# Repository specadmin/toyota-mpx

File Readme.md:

### Description ###

This library is a software driver for MPX (BEAN) bus interface, designed by Toyota and used in some Toyota and Lexus cars. Find the content of the [docs](https://github.com/specadmin/toyota-mpx/tree/master/docs) folder for better understanding of this bus.
The driver works in asynchonous mode and does not block other routings, while MPX packets are being received or transmited.

You may found some MPX packets' description [here](MPX-codes.md).

### Features ###

* Asynchronous receiver
* Asynchronous transmitter
* Independent receiption and transmission
* Arbitration control
* Transmission FIFO queue
* Configurable pins
* Easy timer select

### Physical layer ###

<div align="center">  </div>

### Requirements ###

 * AVR MPU;
 * 12 MHz or higher clock frequency;
 * one external interrupt (PCINT may be used, but not tested yet);
 * one 8 bit timer;
 * GNU AVR C compiller (avr-gcc);

### Limitations ###

 * The driver has NO it's own address. So it receives all the packets, that are being transmited in the MPX network. The driver does NOT filter any packets and does NOT send acknowlegement to any packets.

### Documentation ###

There is no any special documentation for this library. The library code was written to be efficient and clear for your understanding, so it is full of comments. See the [header file](https://github.com/specadmin/toyota-mpx/blob/master/mpx.h) for methods descriptions. Also you may find a [sample project](https://github.com/specadmin/toyota-mpx/tree/master/samples/MPX-dev-board), that uses this library, inside.

### Usage example ###

```
void mpxReceiver(BYTE size, const BYTE* buf)
{
    // make something with received packet

    ...
}

int main()
{
    ...

    mpx_init(mpxReceiver);
    enable_interrupts();

    BYTE data[] = { 0xCD, 0x48 };
    mpx_send(6, 0xFE, sizeof(data), data);

    ...
}
```

### Adding to your project ###

The library is managed as a git submodule. Please refer to git submodule documentation for better understanding.

 * Run the following command in your project's root directory to clone the library:

`git submodule add https://github.com/specadmin/toyota-mpx lib/toyota-mpx`

 * Include the library's header file, where you need it:

`#include "lib/toyota-mpx/mpx.h"`

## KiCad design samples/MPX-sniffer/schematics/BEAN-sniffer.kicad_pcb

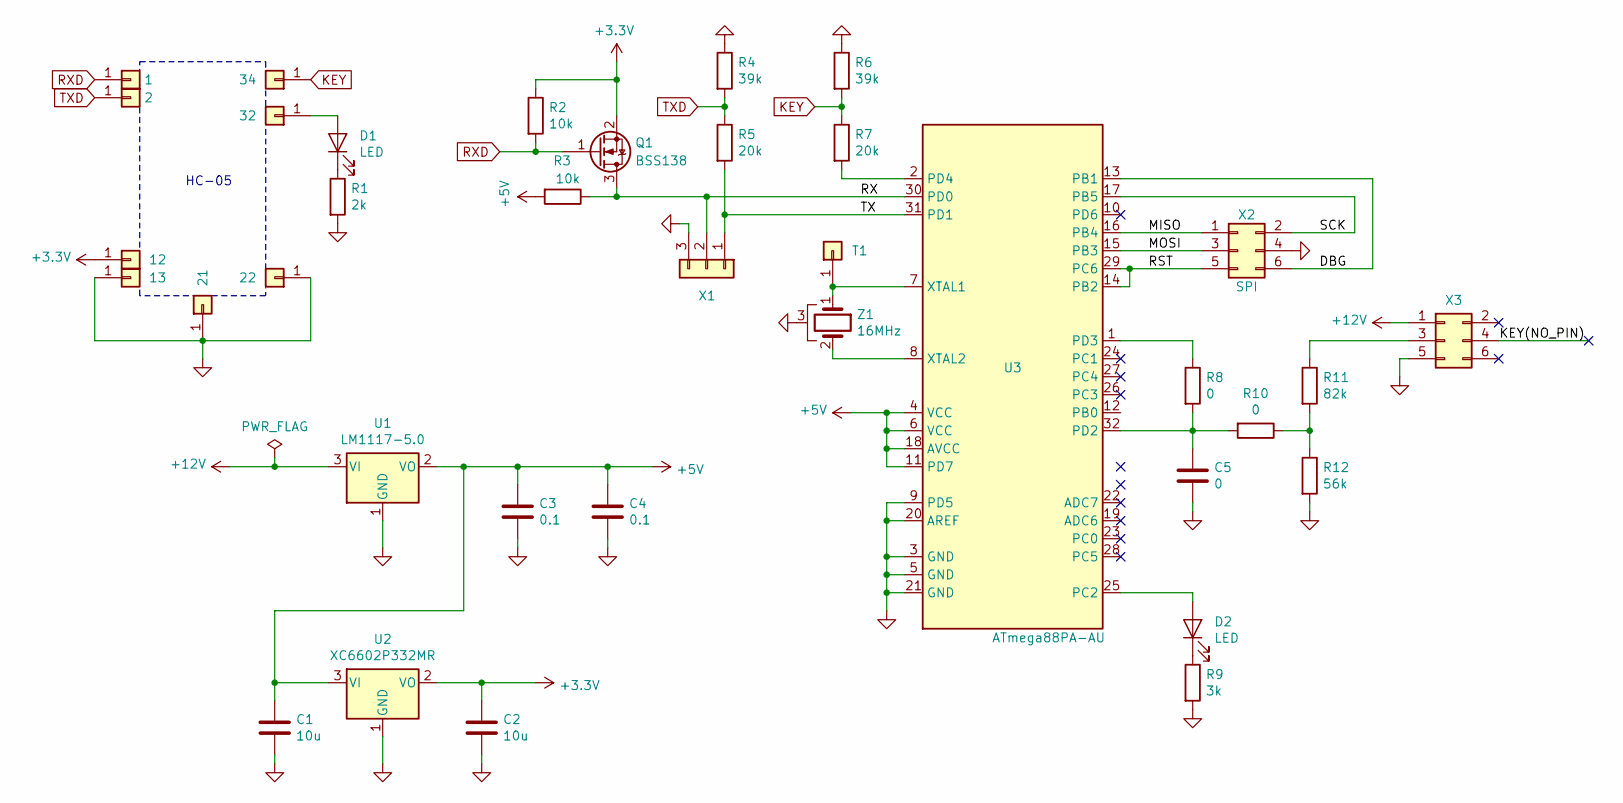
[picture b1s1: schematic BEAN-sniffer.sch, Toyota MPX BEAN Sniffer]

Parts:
C1, C2: 10u; C_0603_1608Metric_Pad1.05x0.95mm_HandSolder
C3, C4: 0.1; C_0603_1608Metric_Pad1.05x0.95mm_HandSolder
C5: 0; C_0603_1608Metric_Pad1.05x0.95mm_HandSolder
D1, D2: LED; LED_0603_1608Metric_Pad1.05x0.95mm_HandSolder
P1, P2, P3, P4, P5, P6, P7, P8: Conn_01x01; TestPoint_THTPad_D1.0mm_Drill0.5mm
Q1: BSS138; SOT-23
R1: 2k; R_0603_1608Metric_Pad1.05x0.95mm_HandSolder
R2, R3: 10k; R_0603_1608Metric_Pad1.05x0.95mm_HandSolder
R4, R6: 39k; R_0603_1608Metric_Pad1.05x0.95mm_HandSolder
R5, R7: 20k; R_0603_1608Metric_Pad1.05x0.95mm_HandSolder
R8, R10: 0; R_0603_1608Metric_Pad1.05x0.95mm_HandSolder
R9: 3k; R_0603_1608Metric_Pad1.05x0.95mm_HandSolder
R11: 82k; R_0603_1608Metric_Pad1.05x0.95mm_HandSolder
R12: 56k; R_0603_1608Metric_Pad1.05x0.95mm_HandSolder
T1: Conn_01x01; TestPoint_Pad_D1.0mm
U1: LM1117-5.0; SOT-223-3_TabPin2
U2: XC6602P332MR; SOT-23
U3: ATmega88PA-AU; TQFP-32_7x7mm_P0.8mm
X1: Conn_01x03; PinHeader_1x03_P2.54mm_Vertical
X2: SPI; PinHeader_2x03_P2.54mm_Vertical
X3: Conn_02x03_Odd_Even; PinHeader_2x03_P2.54mm_Horizontal
Z1: 16MHz; Murata_CSTCExxxxV_3213_crystal

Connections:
+3V3: C2.1, P3.1, Q1.2 (S), R2.1, U2.2 (VO)
+5V: C1.1, C3.1, C4.1, R3.2, U1.2 (VO), U2.3 (VI), U3.4 (VCC), U3.6 (VCC), U3.11 (PD7), U3.18 (AVCC)
+12V: U1.3 (VI), X3.1
/DBG: U3.13 (PB1), X2.6
/KEY(NO_PIN): X3.4
/MISO: U3.16 (PB4), X2.1
/MOSI: U3.15 (PB3), X2.3
/RST: U3.14 (PB2), U3.29 (PC6), X2.5
/RX: Q1.3 (D), R3.1, U3.30 (PD0), X1.2
/SCK: U3.17 (PB5), X2.2
/TX: R5.2, U3.31 (PD1), X1.1
GND: C1.2, C2.2, C3.2, C4.2, C5.2, P4.1, P5.1, P8.1, R1.2, R4.1, R6.1, R9.2, R12.2, U1.1 (GND), U2.1 (GND), U3.3 (GND), U3.5 (GND), U3.9 (PD5), U3.20 (AREF), U3.21 (GND), X1.3, X2.4, X3.5, Z1.3
KEY: P6.1, R6.2, R7.1
unnamed: C5.1, R8.2, R10.2, U3.32 (PD2)
unnamed: D1.1 (K), R1.1
unnamed: D1.2 (A), P7.1
unnamed: D2.1 (K), R9.1
unnamed: D2.2 (A), U3.25 (PC2)
unnamed: R7.2, U3.2 (PD4)
unnamed: R8.1, U3.1 (PD3)
unnamed: R10.1, R11.2, R12.1
unnamed: R11.1, X3.3
unnamed: T1.1, U3.7 (XTAL1), Z1.1
unnamed: U3.8 (XTAL2), Z1.2
RXD: P1.1, Q1.1 (G), R2.2
TXD: P2.1, R4.2, R5.1

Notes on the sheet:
HC-05

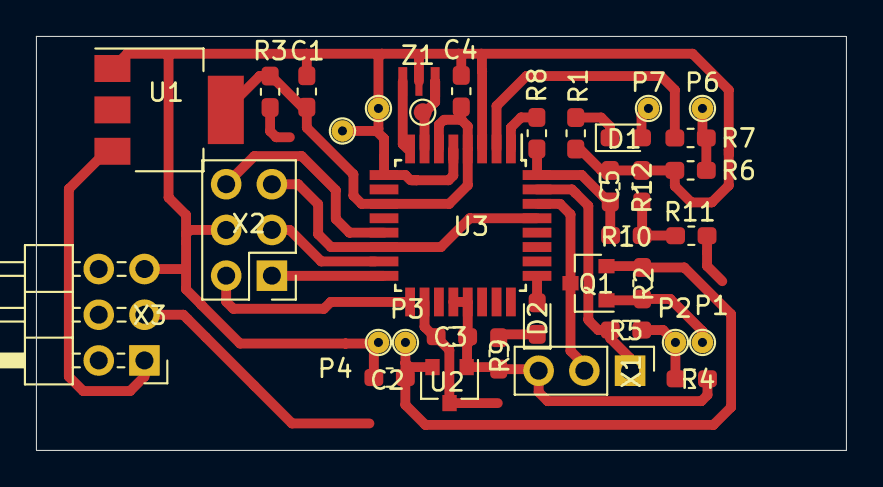
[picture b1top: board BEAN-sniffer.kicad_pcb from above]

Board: 2 copper layers, 45.0 x 23.0 mm, 36 parts (0 on the bottom side), 25 nets.

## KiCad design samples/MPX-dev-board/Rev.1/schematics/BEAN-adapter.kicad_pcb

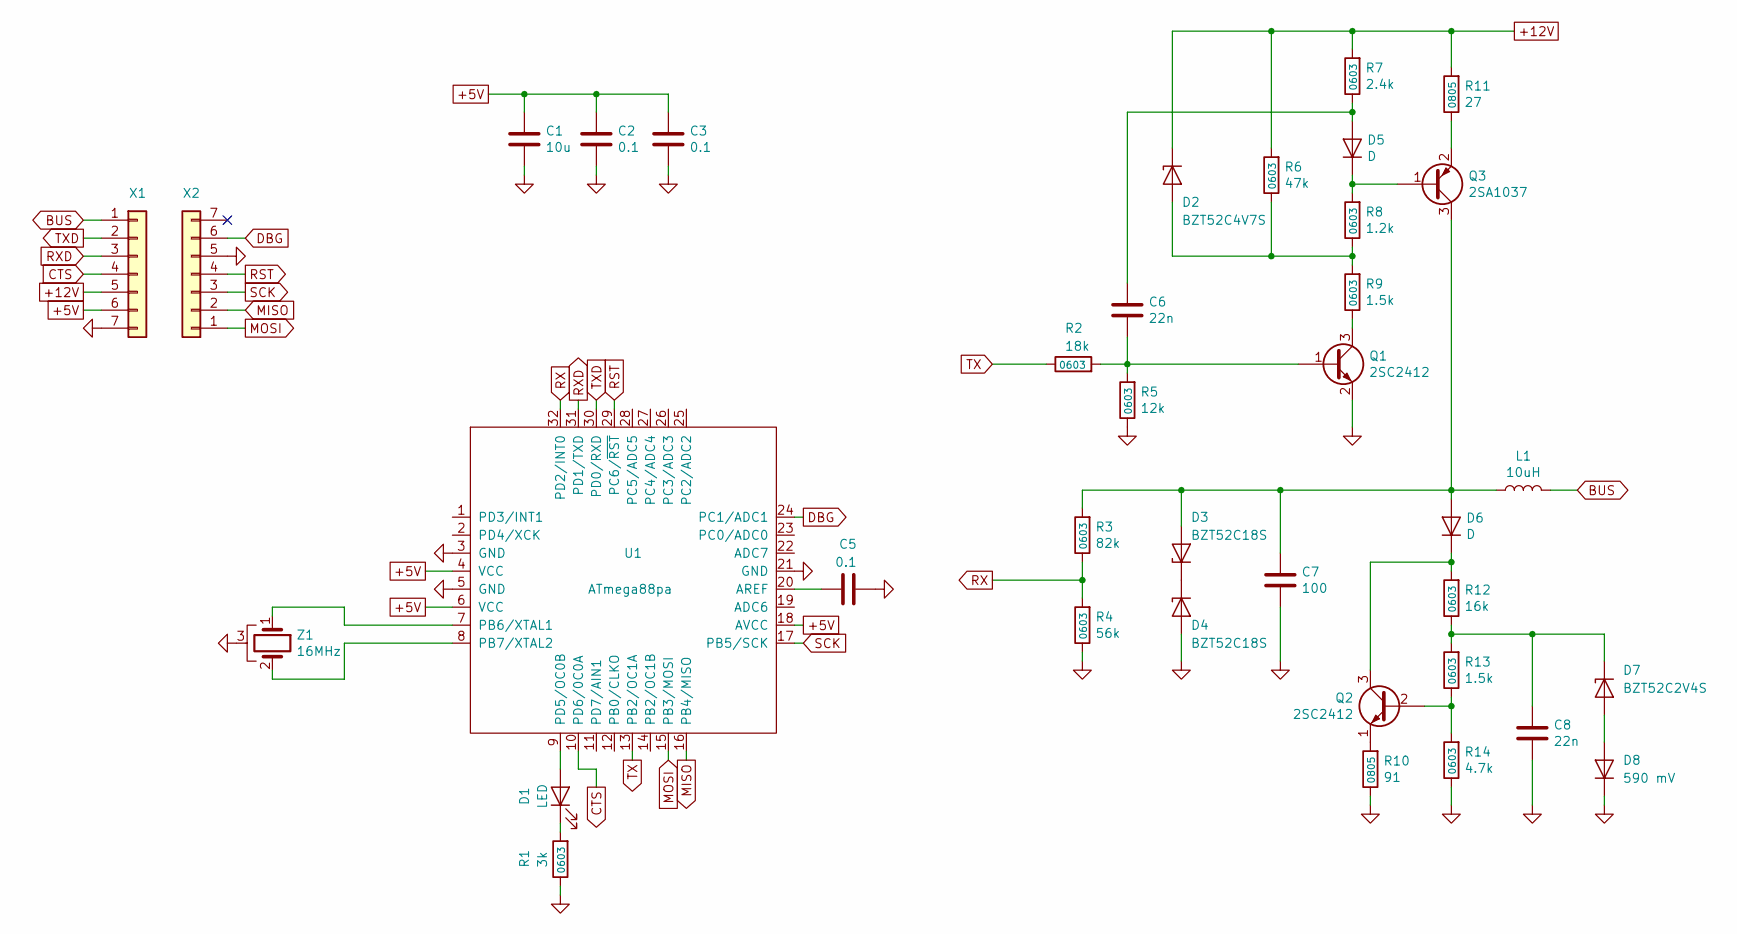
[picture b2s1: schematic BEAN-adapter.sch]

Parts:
C1: 10u; C_0603_1608Metric
C2, C3, C5: 0.1; C_0603_1608Metric
C6, C8: 22n; C_0603_1608Metric
C7: 100; C_0603_1608Metric
D1: LED; LED_0603_1608Metric
D2: BZT52C4V7S; D_SOD-323
D3, D4: BZT52C18S; D_SOD-323
D5: D; D_SOD-323
D6: D; D_SOD-110
D7: BZT52C2V4S; D_SOD-323
D8: 590 mV; D_SOD-323
L1: 10uH; L_Taiyo-Yuden_MD-3030
Q1, Q2: 2SC2412; SOT-23
Q3: 2SA1037; SOT-23
R1: 3k; R_0603_1608Metric
R2: 18k; R_0603_1608Metric
R3: 82k; R_0603_1608Metric
R4: 56k; R_0603_1608Metric
R5: 12k; R_0603_1608Metric
R6: 47k; R_0603_1608Metric
R7: 2.4k; R_0603_1608Metric
R8: 1.2k; R_0603_1608Metric
R9, R13: 1.5k; R_0603_1608Metric
R10: 91; R_0805_2012Metric
R11: 27; R_0805_2012Metric
R12: 16k; R_0603_1608Metric
R14: 4.7k; R_0603_1608Metric
U1: ATmega88pa; TQFP-32_7x7mm_P0.8mm
X1, X2: Conn_01x07; PinHeader_1x07_P2.54mm_Vertical
Z1: 16MHz; Murata_CSTCExxxxV_3213_crystal

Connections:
+5V: C1.1, C2.1, C3.1, U1.4 (VCC), U1.6 (VCC), U1.18 (AVCC), X1.6
+12V: D2.1 (K), R6.2, R7.2, R11.2, X1.5
BUS: L1.2, X1.1
CTS: U1.10 (PD6/0C0A), X1.4
DBG: U1.24 (PC1/ADC1), X2.6
GND: C1.2, C2.2, C3.2, C5.2, C7.2, C8.2, D4.2 (A), D8.1 (K), Q1.2 (E), R1.1, R4.1, R5.1, R10.1, R14.1, U1.3 (GND), U1.5 (GND), U1.21 (GND), X1.7, X2.5, Z1.3
MISO: U1.16 (PB4/MISO), X2.2
MOSI: U1.15 (PB3/MOSI), X2.1
unnamed: C5.1, U1.20 (AREF)
unnamed: C6.1, D5.2 (A), R7.1
unnamed: C6.2, Q1.1 (B), R2.2, R5.2
unnamed: C7.1, D3.2 (A), D6.2 (A), L1.1, Q3.3 (C), R3.2
unnamed: C8.1, D7.1 (K), R12.1, R13.2
unnamed: D1.1 (K), R1.2
unnamed: D1.2 (A), U1.9 (PD5/OC0B)
unnamed: D2.2 (A), R6.1, R8.1, R9.2
unnamed: D3.1 (K), D4.1 (K)
unnamed: D5.1 (K), Q3.1 (B), R8.2
unnamed: D6.1 (K), Q2.3 (C), R12.2
unnamed: D7.2 (A), D8.2 (A)
unnamed: Q1.3 (C), R9.1
unnamed: Q2.1 (E), R10.2
unnamed: Q2.2 (B), R13.1, R14.2
unnamed: Q3.2 (E), R11.1
unnamed: U1.7 (PB6/XTAL1), Z1.1
unnamed: U1.8 (PB7/XTAL2), Z1.2
RST: U1.29 (PC6/~RST), X2.4
RX: R3.1, R4.2, U1.32 (PD2/INT0)
RXD: U1.31 (PD1/TXD), X1.3
SCK: U1.17 (PB5/SCK), X2.3
TX: R2.1, U1.13 (PB2/OC1A)
TXD: U1.30 (PD0/RXD), X1.2

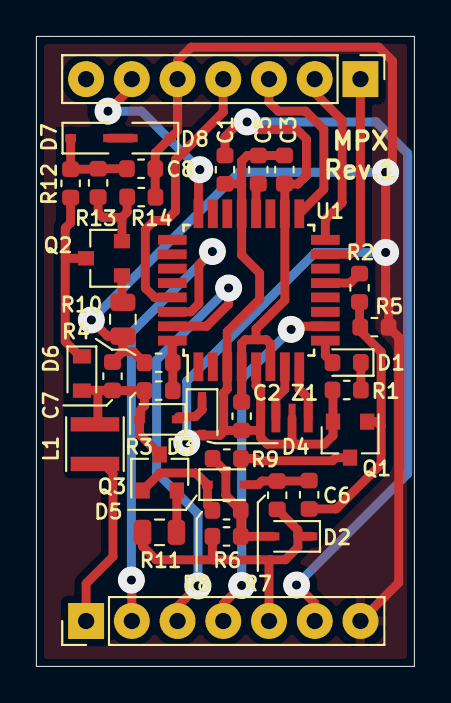
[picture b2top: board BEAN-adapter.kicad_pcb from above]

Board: 2 copper layers, 21.0 x 35.0 mm, 37 parts (0 on the bottom side), 32 nets.

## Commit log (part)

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2020-03-16 Documentation added
2020-03-16 Original devices images added
2020-03-16 Sample project added
2020-03-16 More samples added
2020-03-17 Code cleanup and optimization
    Documentation and optimization
    More optimization and cleanup
    More
2020-03-17 Readme file added
2020-05-07 License added
2020-05-08 Some MPX-codes description added
2020-05-28 MPX codes description updated
2020-06-15 RX LED fix
2020-06-17 Hardware schematics added
2020-06-17 Usage example added
2020-06-17 Schematics width fixed
2020-06-17 Minor improvements for debug
2020-06-18 MPX-codes updated
2020-06-18 Schematics fix
2020-06-18 Simplified timer choice
    Now you need to define MPX_TIMER_ID only
2020-06-20 A new style for MPX-codes description
2020-06-20 Transmission FIFO queue implemented
2020-06-21 Packets description updated
2020-06-21 Description tables fix
2020-06-22 MPX packets description improved
2020-06-26 Minor improvement
2020-07-02 Rear doors examples fix
